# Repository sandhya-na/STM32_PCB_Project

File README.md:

# STM32_PCB_Project
This project contains the complete hardware design files for a custom 2-layer development board built around the STM32F103C8T6 microcontroller. I designed this entire board in KiCad.  My main goal for this project was to focus on real-world board performance—making sure the power lines are stable, the clock signal doesn't pick up electrical noise, and the ground layout is solid enough to prevent signal problems. This board is ready to be used as a reliable core module for robotics or automation setups.
# Design Choices & Technical Details. 
## 1. Power Supply Layout
For the power stage, I used an **AMS1117-3.3V** linear regulator to drop the incoming +5V power down to the +3.3V needed by the STM32 chip. Since these regulators can get pretty hot when running, I spent extra time planning the layout around it.
   - **Cooling Copper Zones**: I poured large areas of copper directly connected to the regulator's ground tab. This acts like a built-in heatsink to keep the regulator cool so it doesn't overheat.
   - **Thicker Power Traces**: I routed the main 3.3V and 5V lines using a wide 0.5mm track width instead of thin signal lines. This keeps the voltage steady and prevents drops when the chip draws sudden bursts of power.
   - **Decoupling Capacitor Placement**: I placed the 100 nF decoupling capacitors as close as physically possible to the STM32's VDD pins. I routed the tracks so that power flows into the capacitor pad first, and then into the chip pin, which helps filter out electrical noise perfectly.
## 2. Crystal Oscillator (Clock) Circuit
The external 8 MHz crystal acts as the heartbeat of the microcontroller. If this part of the circuit picks up noise, the whole chip can freeze or misbehave.
   - **Symmetrical Tracks**: I routed the two lines connecting the crystal to the chip with equal lengths and matching shapes. This ensures the clock signals stay perfectly in sync.
   - **Noise Isolation**: I kept this entire area clear of any other switching digital lines. I didn't route any other tracks underneath the crystal on either layer to prevent noise from leaking into the clock signal.
## 3. Ground Plane & Return Paths
In high-frequency digital circuits, current needs a quick, clean path to travel back to the ground. If the ground path is long and winding, it acts like an antenna and creates a lot of electrical noise.
    - **Solid Bottom Ground Plane**: I used a continuous, unbroken copper pour on the Bottom Layer (B.Cu) to act as a massive ground shield under the whole board.
    - **Dedicated Vias**: Instead of running long ground tracks on the top layer, every ground pad drops immediately down to the bottom ground plane using its own small via. This keeps the connections incredibly short and clean.
# What I Learned
  - **Manual Routing Control**: Hand-routing 100% of the tracks allowed me to plan exactly where current flows, ensuring my bottom ground plane didn't get chopped into pieces by crossing traces.
  - **Handling Bottlenecks**: I learned how to deal with tight spaces around small 0805 components by smoothly narrowing down traces just to pass the bottleneck, and then widening them back out for power capacity.
  - **Fixing DRC Errors**: Running the final Design Rules Check taught me how to fix real manufacturing issues, like snapping open edges on the board outline layer and clearing up solder mask alerts near the crystal pads.

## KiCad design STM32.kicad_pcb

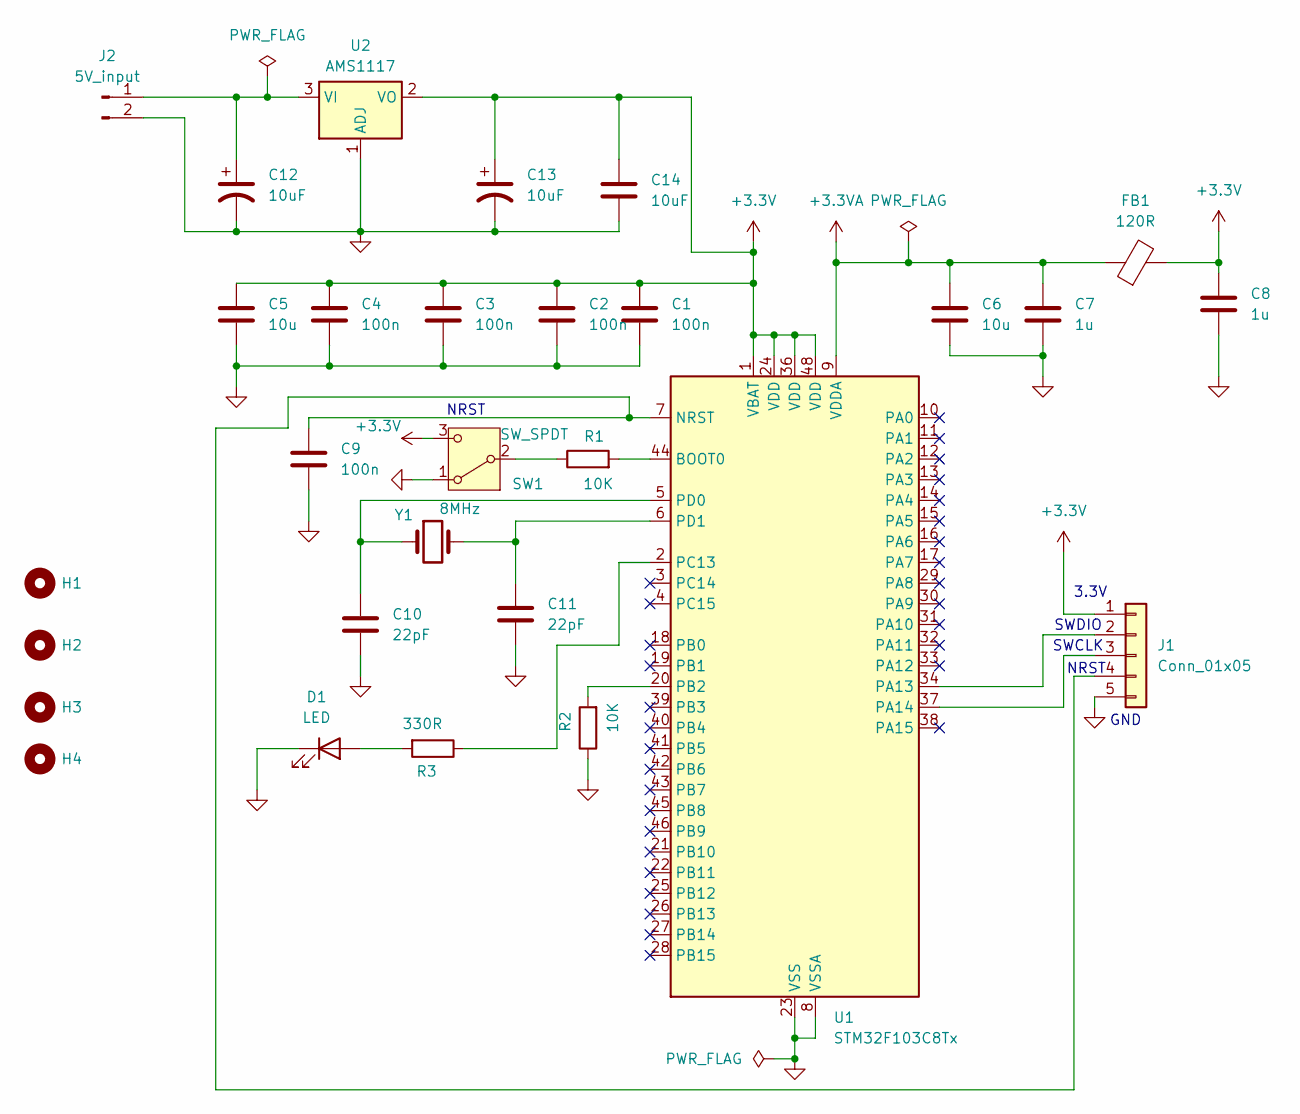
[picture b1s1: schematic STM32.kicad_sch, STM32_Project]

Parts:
C1, C2, C3, C4, C9: 100n; C_0805_2012Metric
C5: 10u; C_0805_2012Metric
C6: 10u; C_1206_3216Metric
C7, C8: 1u; C_0805_2012Metric
C10, C11: 22pF; C_0805_2012Metric
C12, C13: 10uF; C_1206_3216Metric
C14: 10uF; C_0805_2012Metric
D1: LED; D_0805_2012Metric
FB1: 120R; R_0805_2012Metric
H1, H2, H3, H4: MountingHole_2.2mm_M2
J1: Conn_01x05; PinHeader_1x05_P2.54mm_Vertical
J2: 5V_input; PinHeader_1x02_P2.54mm_Vertical
R1, R2: 10K; R_0805_2012Metric
R3: 330R; R_0805_2012Metric
SW1: SW_SPDT; SW_Lever_1P2T_NKK_GW12LxH
U1: STM32F103C8Tx; LQFP-48_7x7mm_P0.5mm
U2: AMS1117; SOT-223-3_TabPin2
Y1: 8MHz; Crystal_SMD_5032-4Pin_5.0x3.2mm

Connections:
+3.3V: C1.1, C2.1, C3.1, C4.1, C5.1, C8.1, C13.1, C14.1, FB1.2, J1.1, SW1.3 (C), U1.1 (VBAT), U1.24 (VDD), U1.36 (VDD), U1.48 (VDD), U2.2 (VO)
+3.3VA: C6.1, C7.1, FB1.1, U1.9 (VDDA)
GND: C1.2, C2.2, C3.2, C4.2, C5.2, C6.2, C7.2, C8.2, C9.2, C10.2, C11.2, C12.2, C13.2, C14.2, D1.1 (K), J1.5, J2.2, R2.1, SW1.1 (A), U1.8 (VSSA), U1.23 (VSS), U1.35 (VSS), U1.47 (VSS), U2.1 (ADJ)
unnamed: D1.2 (A), R3.2
unnamed: J1.2, U1.34 (PA13)
unnamed: J1.3, U1.37 (PA14)
unnamed: C9.1, J1.4, U1.7 (NRST)
unnamed: C12.1, J2.1, U2.3 (VI)
unnamed: R1.1, SW1.2 (B)
unnamed: R1.2, U1.44 (BOOT0)
unnamed: R2.2, U1.20 (PB2)
unnamed: R3.1, U1.2 (PC13)
unnamed: C10.1, U1.5 (PD0), Y1.1
unnamed: C11.1, U1.6 (PD1), Y1.2

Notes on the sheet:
SWDIO
NRST
NRST
3.3V
SWCLK
GND

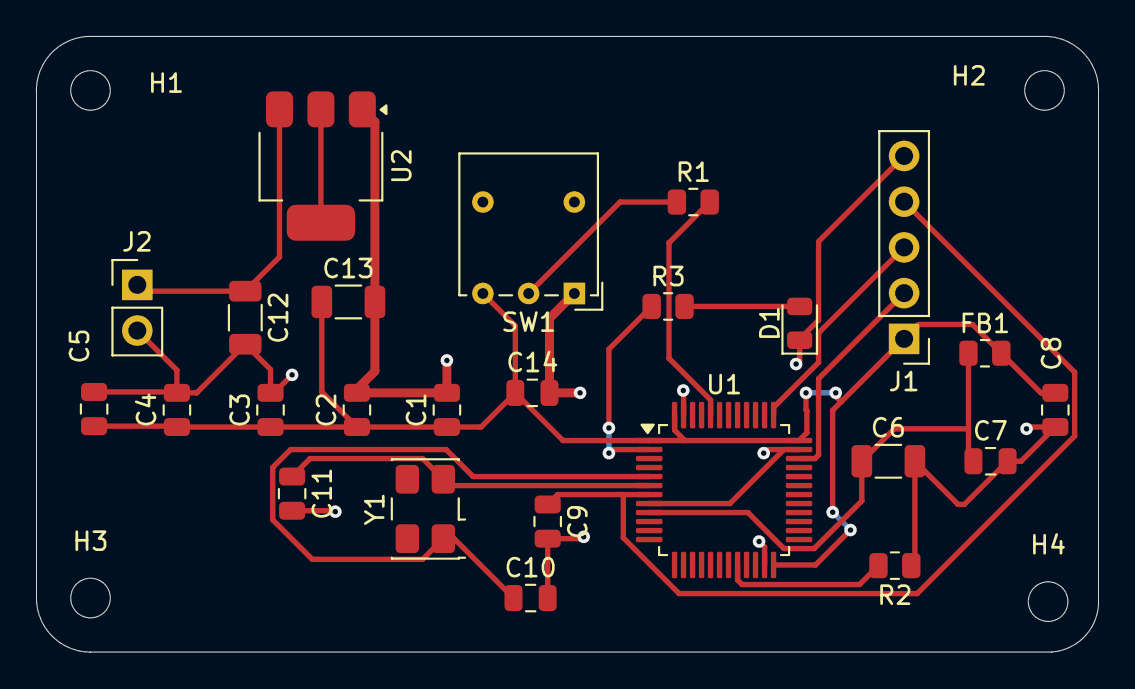
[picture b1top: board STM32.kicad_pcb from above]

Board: 2 copper layers, 59.0 x 34.2 mm, 29 parts (0 on the bottom side), 14 nets.

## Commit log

2026-05-27 Create temp
